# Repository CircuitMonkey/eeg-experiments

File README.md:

# eeg-experiments
Experiments in EEG hardware and software.

<h2>EEG Single Channel CHiPz Module</h2>
The single channel module for EEG input is designed as a SMT CHiPz module for integration into larger designs.  It features an optimized and lower cost version of the [Upside Down Labs BioAmp EXG Pill](https://github.com/upsidedownlabs/bioAmp-exg-pill).  For our design, we removed some configuration options such that the user would opt to simply modify the components on the board for the specific purpose such as EEG/EOG/EKG/etc.

<h2>Example/Test Carrier for EEG Single Channel CHiPz Module</h2>
We made a simple carrier PCB for the single channel EEG sensor CHiPz module so that we could test it as well as its easy use in a prototyping environment.  We also made a KiCAD symbol and footprint for the module so that you can integrate the module into your own PCB designs. The CHiPz KiCAD symbol and footprint library is located in separate [ GIT Hub repo ](https://github.com/circuitmonkey/kicad-library). That repo also includes many KiCAD components that we have created or tuned to be superior to the standard KiCAD components.

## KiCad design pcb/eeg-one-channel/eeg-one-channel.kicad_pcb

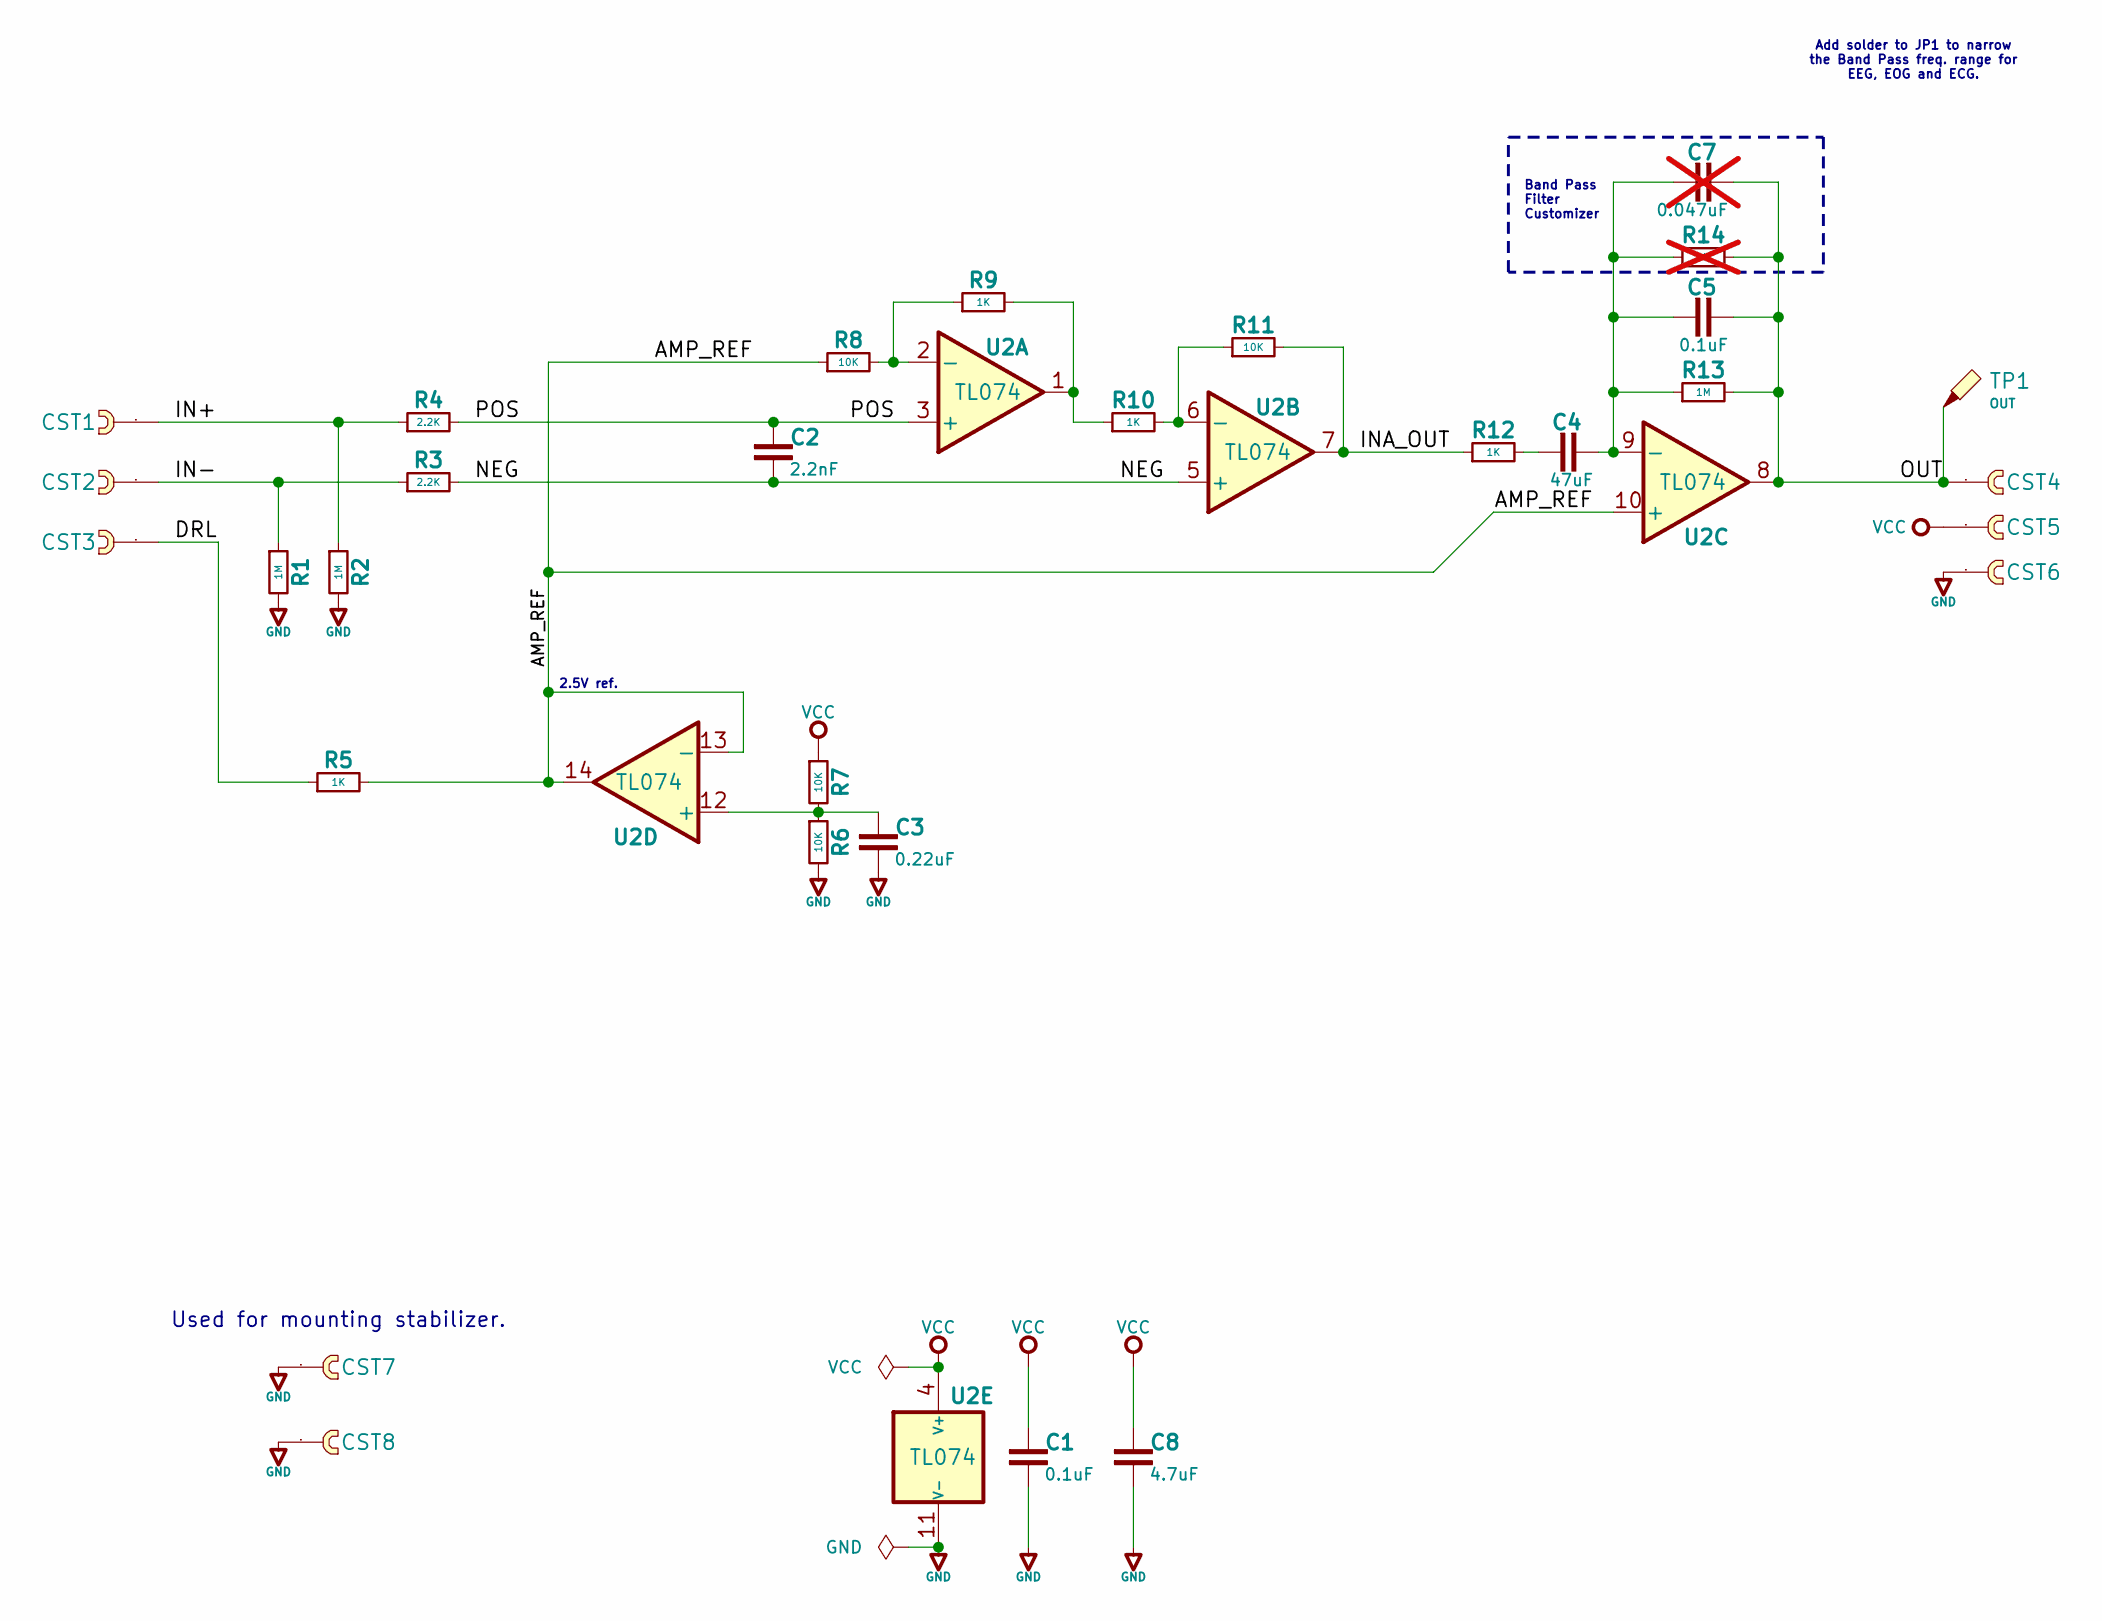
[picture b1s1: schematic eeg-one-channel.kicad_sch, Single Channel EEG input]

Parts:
C1, C5: 0.1uF; C_0603_1608Metric
C2: 2.2nF; C_0603_1608Metric
C3: 0.22uF; C_0603_1608Metric
C4: 47uF; C_0603_1608Metric
C7: 0.047uF; C_0603_1608Metric; not fitted
C8: 4.7uF; C_0603_1608Metric
CST1: IN+; cast-2.0-01P
CST2: IN-; cast-2.0-01P
CST3: REF; cast-2.0-01P
CST4: OUT; cast-2.0-01P
CST5: Vcc; cast-2.0-01P
CST6, CST7, CST8: GND; cast-2.0-01P
R1, R2, R13: 1M; R_0603_1608Metric
R3, R4: 2.2K; R_0603_1608Metric
R5, R9, R10, R12: 1K; R_0603_1608Metric
R6, R7, R8, R11: 10K; R_0603_1608Metric
R14: 1M; R_0603_1608Metric; not fitted
TP1: OUT; TestPoint_Pad_1.5x1.5mm
U2: TL074; SO-14_3.9x8.65mm_P1.27mm; MPN TL074HIDR

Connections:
/AMP_REF: R5.2, R8.1, U2.10 (+), U2.13 (-), U2.14
/DRL: CST3.1, R5.1
/IN+: CST1.1, R2.1, R4.1
/IN-: CST2.1, R1.1, R3.1
/INA_OUT: R11.2, R12.1, U2.7
/NEG: C2.2, R3.2, U2.5 (+)
/OUT: C5.2, C7.2, CST4.1, R13.2, R14.2, TP1.1 (1_1), U2.8
/POS: C2.1, R4.2, U2.3 (+)
GND: C1.2, C3.2, C8.2, CST6.1, CST7.1, CST8.1, R1.2, R2.2, R6.2, U2.11 (V-)
unnamed: C4.1, R12.2
unnamed: R9.2, R10.1, U2.1
unnamed: R8.2, R9.1, U2.2 (-)
unnamed: R10.2, R11.1, U2.6 (-)
unnamed: C4.2, C5.1, C7.1, R13.1, R14.1, U2.9 (-)
unnamed: C3.1, R6.1, R7.2, U2.12 (+)
VCC: C1.1, C8.1, CST5.1, R7.1, U2.4 (V+)

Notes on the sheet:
Add solder to JP1 to narrow the Band Pass freq. range for EEG, EOG and ECG.
Used for mounting stabilizer.
Band Pass Filter Customizer
2.5V ref.

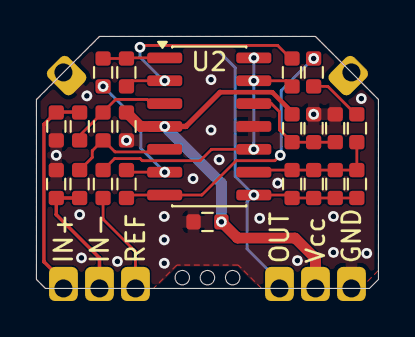
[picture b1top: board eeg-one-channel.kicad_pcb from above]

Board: 2 copper layers, 19.0 x 14.0 mm, 31 parts (1 on the bottom side), 16 nets.

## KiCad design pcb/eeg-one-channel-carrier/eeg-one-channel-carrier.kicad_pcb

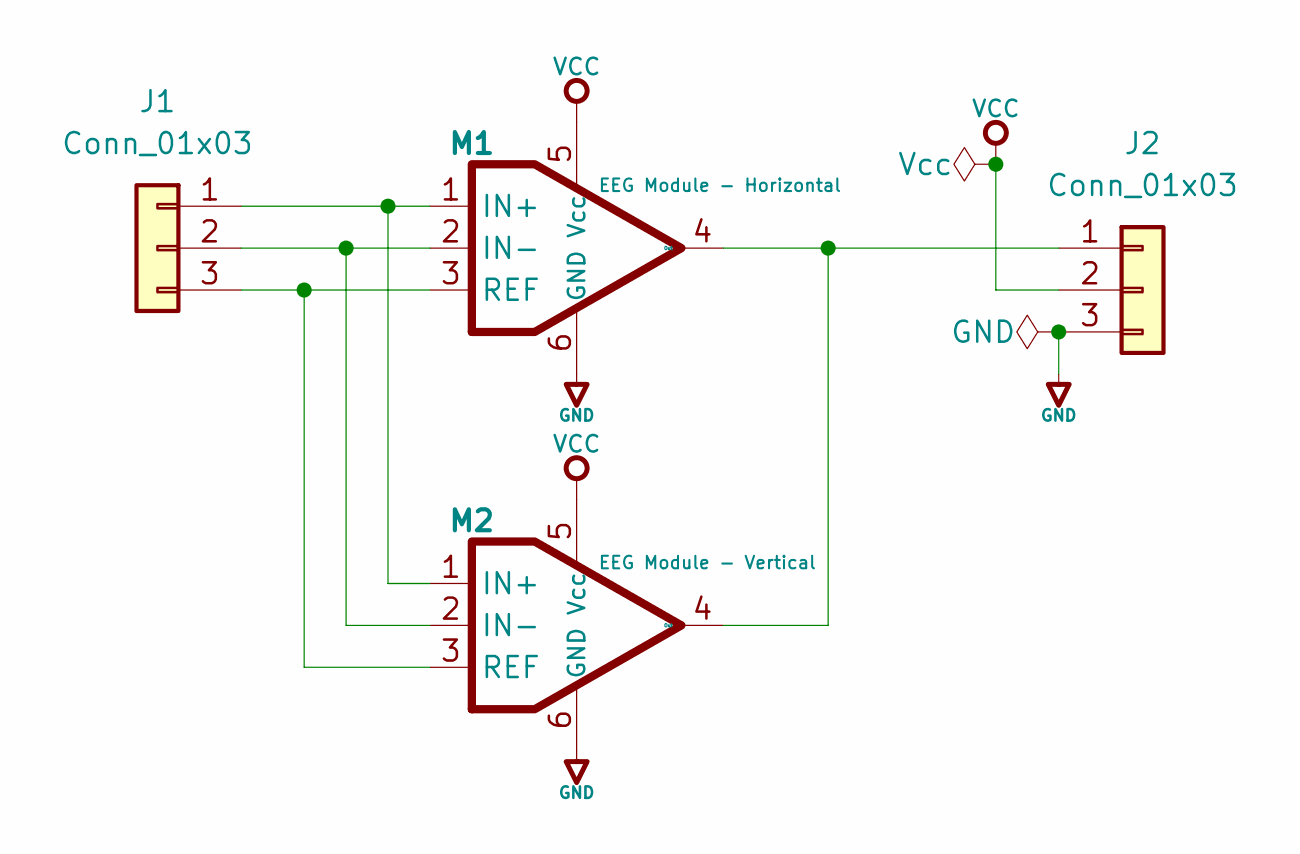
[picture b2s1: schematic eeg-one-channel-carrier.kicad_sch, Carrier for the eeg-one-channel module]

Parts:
J1, J2: Conn_01x03; PinHeader_1x03_P2.54mm_Vertical
M1: EEG Module - Horizontal; eeg-one-channel
M2: EEG Module - Vertical; eeg-one-channel_vert

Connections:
GND: J2.3, M1.6 (GND), M2.6 (GND)
unnamed: J1.1, M1.1 (IN+), M2.1 (IN+)
unnamed: J1.2, M1.2 (IN-), M2.2 (IN-)
unnamed: J1.3, M1.3 (REF), M2.3 (REF)
unnamed: J2.1, M1.4 (Out), M2.4 (Out)
VCC: J2.2, M1.5 (Vcc), M2.5 (Vcc)

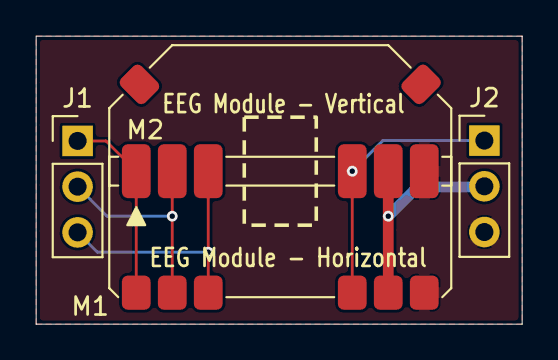
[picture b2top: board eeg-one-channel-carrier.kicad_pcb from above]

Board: 2 copper layers, 27.0 x 16.0 mm, 4 parts (0 on the bottom side), 6 nets.

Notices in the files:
pcb/eeg-one-channel-carrier/eeg-one-channel-carrier.kicad_pcb:
License: MIT
pcb/eeg-one-channel/eeg-one-channel.kicad_sch:
MIT License
